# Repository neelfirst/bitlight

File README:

h1. bitlight

bitlight is an ultra-portable digital tealight.
- battery life: ~100 min
- color: warm white
- connectivity: none
- usb-c rechargeable
- serviceable battery
- one pot control

future revisions.
- speed up battery charging with a prod-grade IC
- get a thumbwheel that clicks to turn on
- add or replace with inductive charging
- fix the USB-C connector, no trusty sparkfun

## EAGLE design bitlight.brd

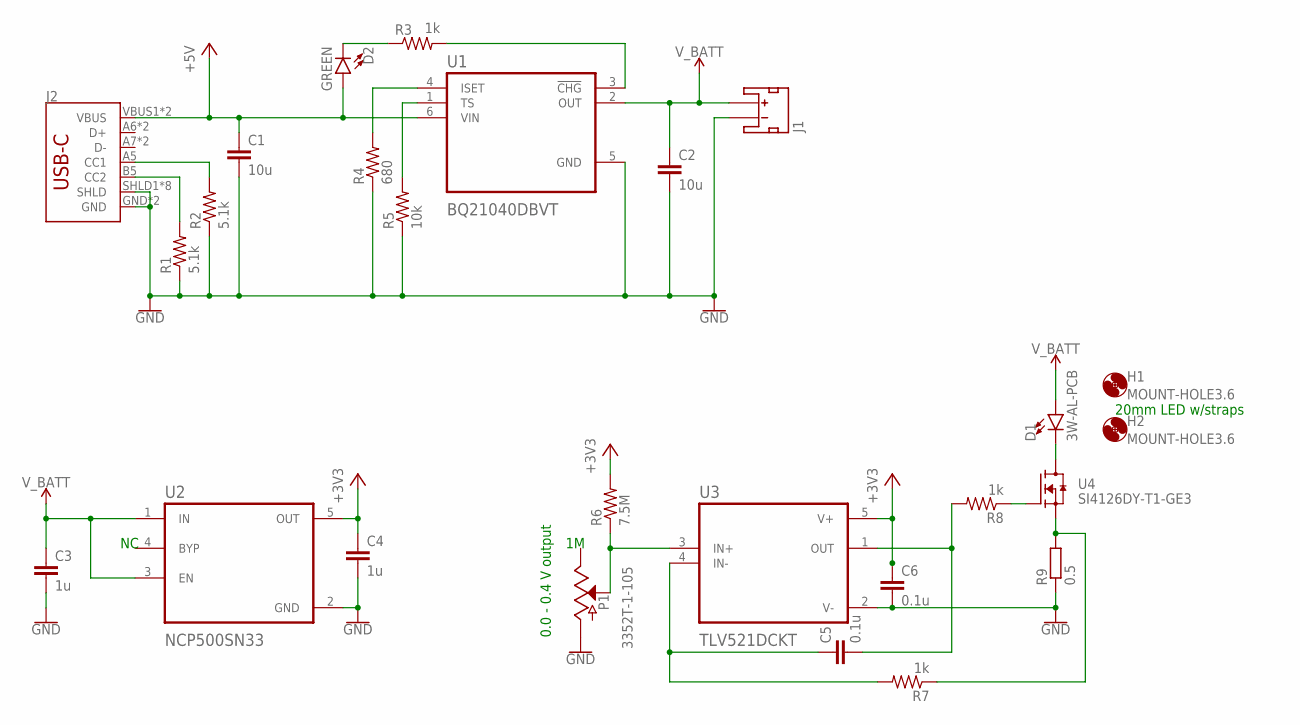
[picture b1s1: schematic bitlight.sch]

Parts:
C1, C2: 10u; C0603
C3, C4: 1u; C0603
C5, C6: 0.1u; C0603
D1: 3W-AL-PCB; AL-PCB-20MM
D2: GREEN; LED-0603
H1, H2: MOUNT-HOLE3.6; 3,6
J1: JST_2MM_MALE; JST-2-SMD
J2: USB_C16PIN; USB-C-16P
P1: 3352T-1-105; 3352T-1
R1, R2: 5.1k; R0603
R3, R7, R8: 1k; R0603
R4: 680; R0603
R5: 10k; R0603
R6: 7.5M; R0603
R9: 0.5; R2512
U1: BQ21040DBVT; SOT95P280X145-6N
U2: NCP500SN33; SOT95P280X145-5N
U3: TLV521DCKT; SOT65P210X110-5N
U4: SI4126DY-T1-GE3; SOIC127P600X175-8N

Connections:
+3V3: C4.1, C6.1, R6.2, U2.5 (OUT), U3.5 (V+)
+5V: C1.1, D2.A, J2.VBUS1 (VBUS), J2.VBUS2 (VBUS), U1.6 (VIN)
GND: C1.2, C2.2, C3.2, C4.2, C6.2, J1.1 (-), J2.GND, J2.GND2 (GND), J2.SHLD1 (SHLD), J2.SHLD2 (SHLD), J2.SHLD3 (SHLD), J2.SHLD4 (SHLD), J2.SHLD5 (SHLD), J2.SHLD6 (SHLD), J2.SHLD7 (SHLD), J2.SHLD8 (SHLD), P1.CCW (A), R1.1, R2.1, R4.1, R5.1, R9.1, U1.5 (GND), U2.2 (GND), U3.2 (V-)
unnamed: R3.2, U1.3 (!CHG)
unnamed: C5.1, R7.2, U3.4 (IN-)
unnamed: D1.- (C), U4.5 (D), U4.6 (D), U4.7 (D), U4.8 (D)
unnamed: D2.C, R3.1
unnamed: R7.1, R9.2, U4.1 (S), U4.2 (S), U4.3 (S)
unnamed: C5.2, R8.2, U3.1 (OUT)
unnamed: J2.B5 (CC2), R1.2
unnamed: R8.1, U4.4 (G)
unnamed: P1.WIPE (S), R6.1, U3.3 (IN+)
unnamed: J2.A5 (CC1), R2.2
PROG: R4.2, U1.4 (ISET)
THERM: R5.2, U1.1 (TS)
V_BATT: C2.1, C3.1, D1.+ (A), J1.2 (+), U1.2 (OUT), U2.1 (IN), U2.3 (EN)

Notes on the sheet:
0.0 - 0.4 V output
20mm LED w/straps

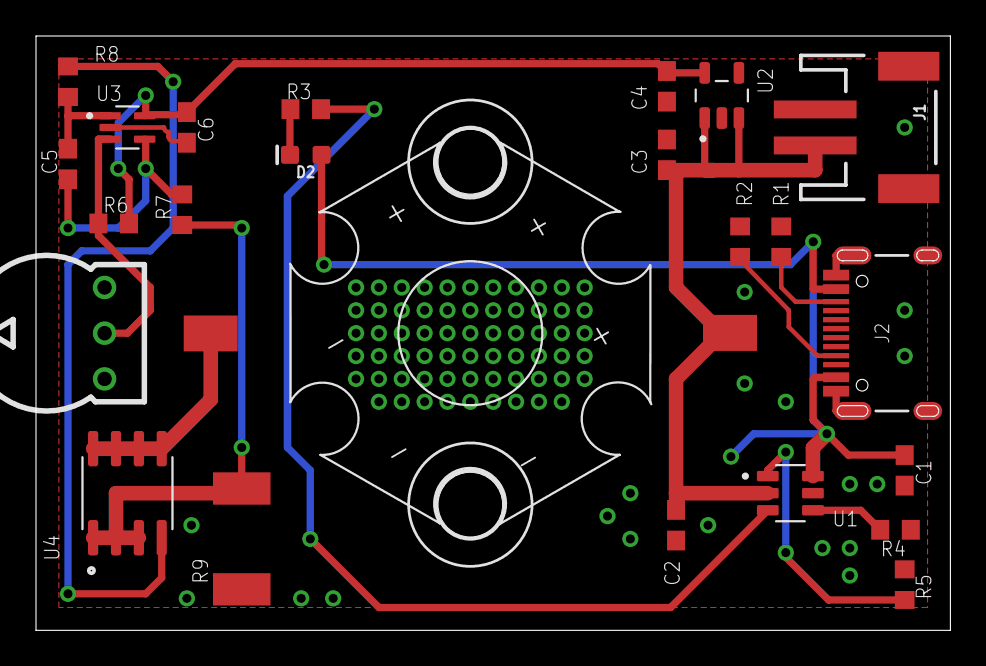
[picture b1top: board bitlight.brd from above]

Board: 2 copper layers, 50.8 x 33.0 mm, 26 parts (0 on the bottom side), 16 nets.

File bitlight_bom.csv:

Qty,Part,Value,Device,Package,Description
2,C1;C2,10u,C-EUC0603,C0603,"CAPACITOR, European symbol"
2,C3;C4,1u,C-EUC0603,C0603,"CAPACITOR, European symbol"
2,C5;C6,0.1u,C-EUC0603,C0603,"CAPACITOR, European symbol"
1,D1,3W-AL-PCB,3W-AL-PCB,AL-PCB-20MM,
1,D2,GREEN,LED-GREEN0603,LED-0603,Green SMD LED
1,J1,,JST_2MM_MALE,JST-2-SMD,JST 2MM MALE RA CONNECTOR
1,J2,,USB_C16PIN,USB-C-16P,USB Type C 16Pin Connector
1,P1,3352T-1-105,3352T-1,3352T-1,
2,R1; R2,5.1k,R-US_R0603,R0603,"RESISTOR, American symbol"
3,R3; R7; R8,1k,R-US_R0603,R0603,"RESISTOR, American symbol"
1,R4,680r,R-US_R0603,R0603,"RESISTOR, American symbol"
1,R5,10k,R-US_R0603,R0603,"RESISTOR, American symbol"
1,R6,7.5M,R-US_R0603,R0603,"RESISTOR, American symbol"
1,R9,0.5r,R-EU_R2512,R2512,"RESISTOR, European symbol"
1,U1,BQ21040DBVT,BQ21040DBVT,SOT95P280X145-6N,Check prices
1,U2,NCP500SN33,MIC5205YM5,SOT95P280X145-5N,None Check prices
1,U3,TLV521DCKT,TLV521DCKT,SOT65P210X110-5N,Check prices
1,U4,SI4126DY-T1-GE3,SI4126DY-T1-GE3,SOIC127P600X175-8N,Single N-Channel 30 V 0.00275 Ohm
2,Z1;Z2,Jumper,,,

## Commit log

2021-01-24 initial schematics
2021-01-24 initial readme
2021-01-24 removing sch
2021-02-14 added charger submodule, complete design
2021-02-15 final design
2021-02-15 readme update
2021-02-16 bom update

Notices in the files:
parts and their libraries:
SparkFun-LED: Licensing: Creative Commons ShareAlike 4.0 International - https://creativecommons.org/licenses/by-sa/4.0
